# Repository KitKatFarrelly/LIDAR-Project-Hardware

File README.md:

# What is this??
This is the KiCAD files for the PCB and schematic of several iterations of my LIDAR sensor board.
The goal of this board is a wifi-enabled LIDAR sensor that also collects direction and acceleration data via IMU and can act as a flight controller.

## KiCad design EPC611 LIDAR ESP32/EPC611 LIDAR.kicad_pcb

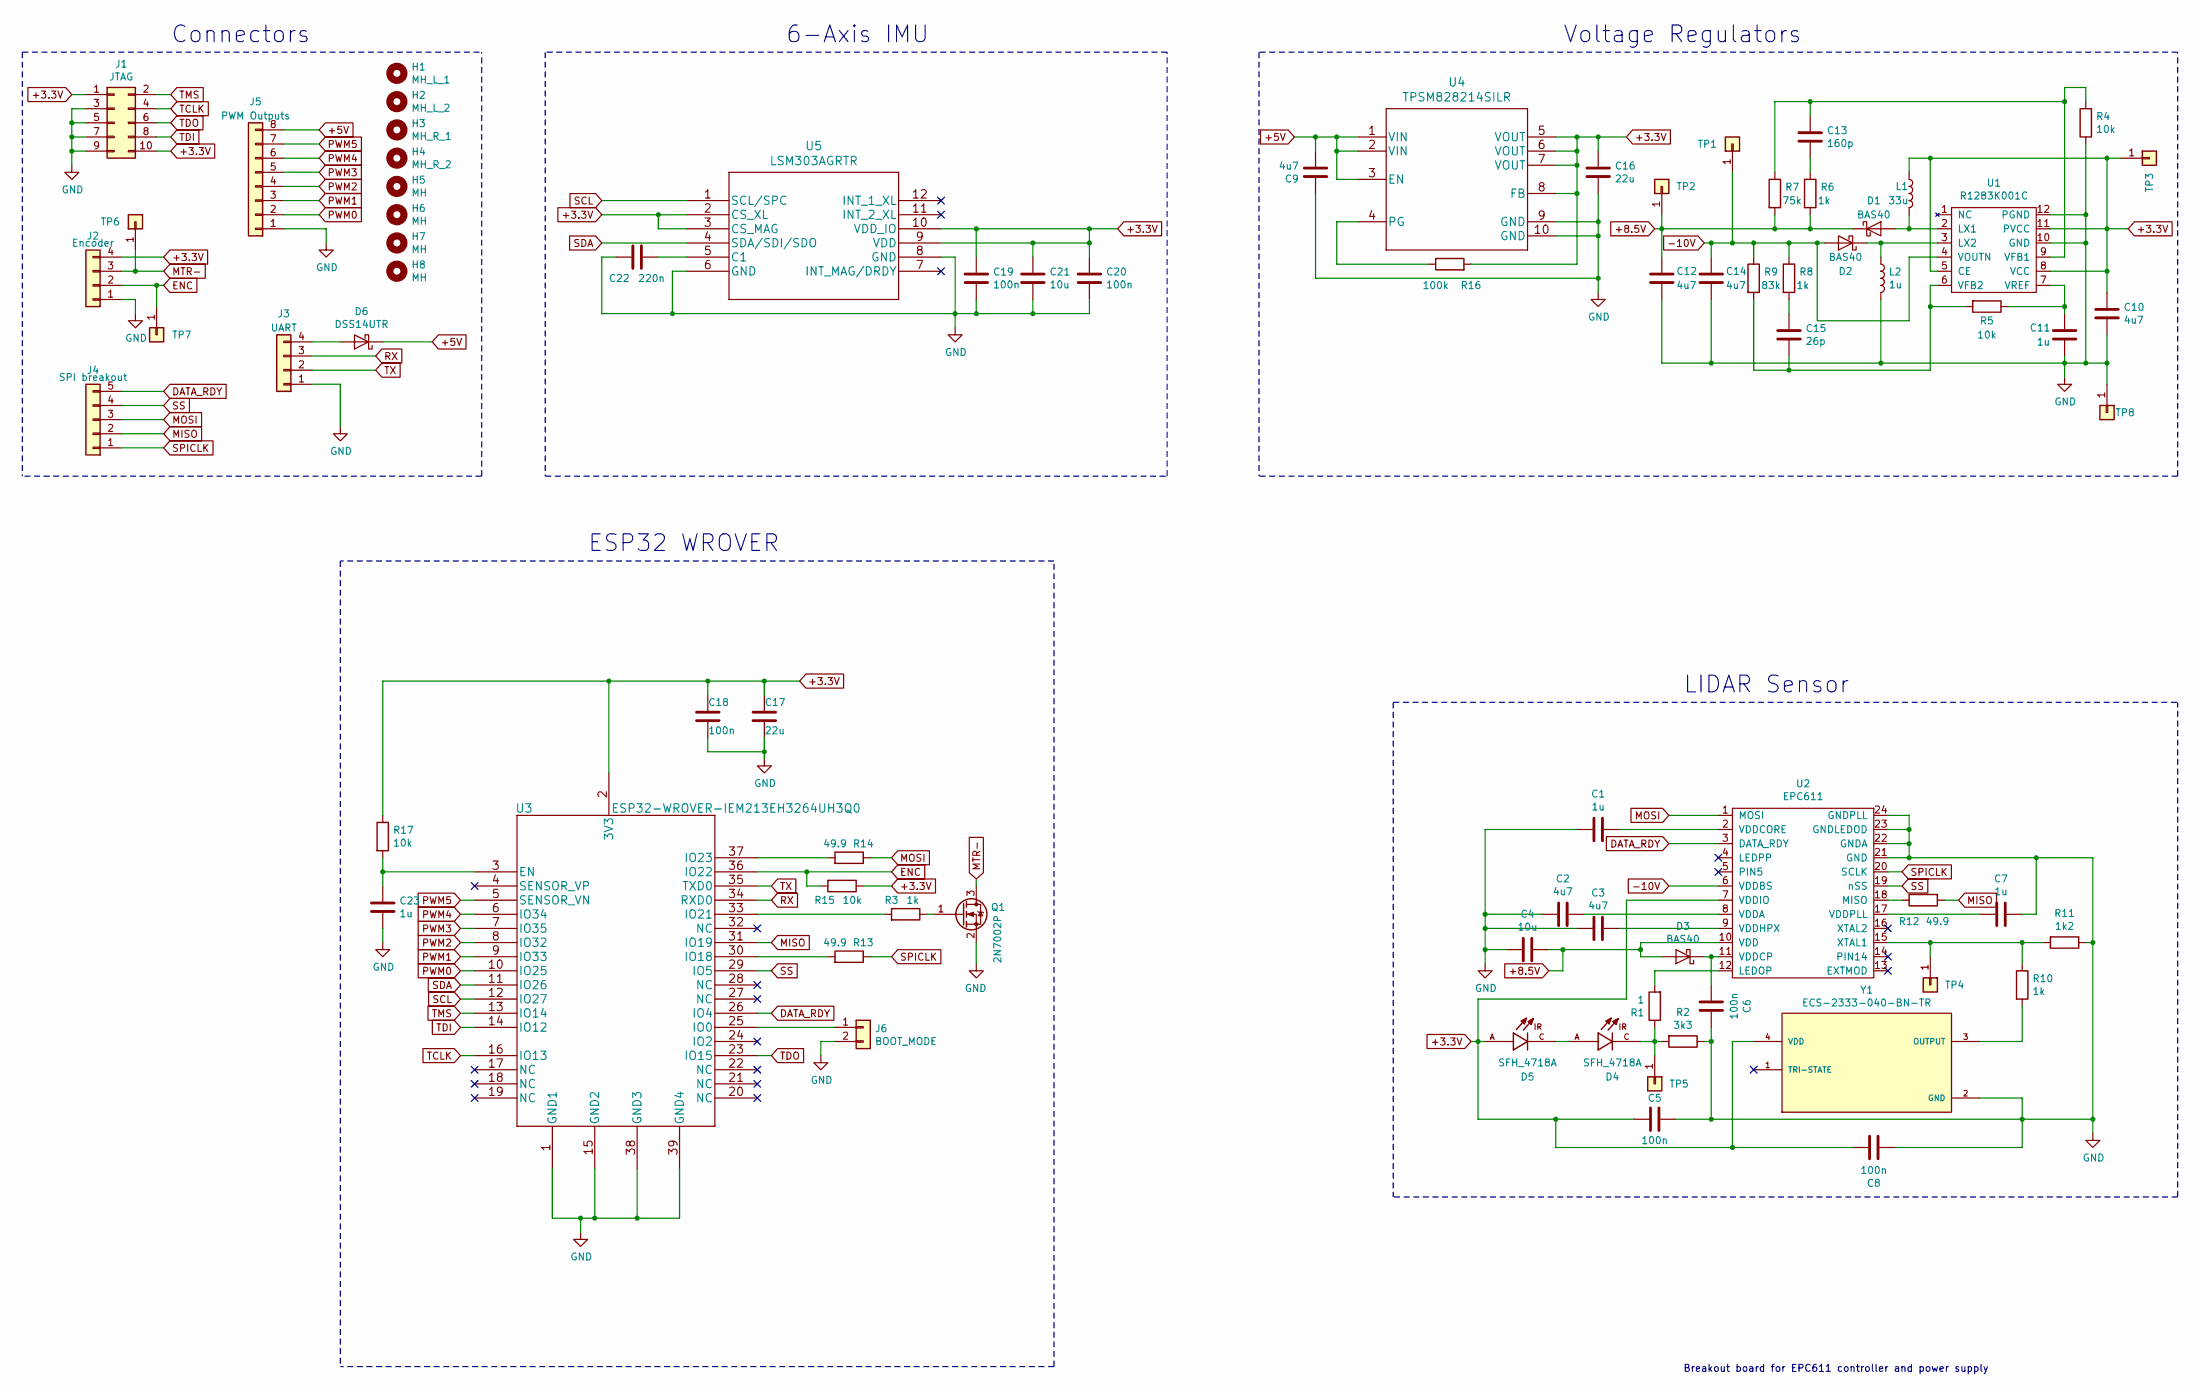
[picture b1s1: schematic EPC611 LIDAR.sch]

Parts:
C1, C7, C11, C23: 1u; C_0603_1608Metric
C2, C3, C9, C10, C12, C14: 4u7; C_0603_1608Metric
C4, C21: 10u; C_0805_2012Metric
C5, C6, C8, C18, C19, C20: 100n; C_0402_1005Metric
C13: 160p; C_0402_1005Metric
C15: 26p; C_0402_1005Metric
C16, C17: 22u; C_0805_2012Metric
C22: 220n; C_0402_1005Metric
D1, D2, D3: BAS40; D_SOT-23_ANK
D4, D5: SFH_4718A; LED_SFH_4718A; PARTREV 1.4
D6: DSS14UTR; D_SOD-123F
H1: MH_L_1; MountingHole_2.2mm_M2
H2: MH_L_2; MountingHole_2.2mm_M2
H3: MH_R_1; MountingHole_2.2mm_M2
H4: MH_R_2; MountingHole_2.2mm_M2
H5, H6, H7, H8: MH; MountingHole_3.2mm_M3
J1: JTAG; PinHeader_2x05_P1.27mm_Vertical_SMD
J2: Encoder; Molex_PicoBlade_53261-0471_1x04-1MP_P1.25mm_Horizontal
J3: UART; Molex_PicoBlade_53261-0471_1x04-1MP_P1.25mm_Horizontal
J4: SPI breakout; spi line debug
J5: PWM Outputs; Molex_PicoBlade_53261-0871_1x08-1MP_P1.25mm_Horizontal
J6: BOOT_MODE; PinHeader_1x02_P1.00mm_Vertical
L1: 33u; L_1008_2520Metric
L2: 1u; L_0603_1608Metric
Q1: 2N7002P; SOT-23
R1: 1; R_0805_2012Metric
R2: 3k3; R_0402_1005Metric
R3, R6, R8, R10: 1k; R_0402_1005Metric
R4, R5, R15, R17: 10k; R_0402_1005Metric
R7: 75k; R_0402_1005Metric
R9: 83k; R_0402_1005Metric
R11: 1k2; R_0402_1005Metric
R12, R13, R14: 49.9; R_0402_1005Metric
R16: 100k; R_0201_0603Metric
TP1, TP2, TP3, TP4, TP5, TP6, TP7, TP8: Conn_01x01; test point
U1: R1283K001C; R1283x
U2: EPC611
U3: ESP32-WROVER-IEM213EH3264UH3Q0
U4: TPSM828214SILR
U5: LSM303AGRTR
Y1: ECS-2333-040-BN-TR; OSC_ECS-2333-040-BN-TR; PARTREV N/A

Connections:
+3.3V: C5.2, C8.1, C10.1, C16.1, C17.1, C18.1, C19.1, C20.1, C21.1, D5.A, J1.1, J1.10, J2.4, L1.1, R15.1, R16.2, R17.1, TP3.1, U1.5 (CE), U1.8 (VCC), U1.11 (PVCC), U2.7 (VDDIO), U3.2 (3V3), U4.5 (VOUT), U4.6 (VOUT), U4.7 (VOUT), U4.8 (FB), U5.2 (CS_XL), U5.3 (CS_MAG), U5.9 (VDD), U5.10 (VDD_IO), Y1.4 (VDD)
+5V: C9.2, D6.1 (K), J5.8, U4.1 (VIN), U4.2 (VIN), U4.3 (EN)
+8.5V: C4.1, C12.1, D1.1 (K), D3.2 (A), R6.2, R7.2, TP2.1, U2.10 (VDD)
-10V: C14.1, D2.2 (A), R8.1, R9.1, TP1.1, U1.4 (VOUTN), U2.6 (VDDBS)
DATA_RDY: J4.5, U2.3 (DATA_RDY), U3.26 (IO4)
ENC: J2.2, R15.2, TP7.1, U3.36 (IO22)
GND: C1.2, C2.2, C3.2, C4.2, C5.1, C6.1, C7.1, C8.2, C9.1, C10.2, C11.2, C12.2, C14.2, C16.2, C17.2, C18.2, C19.2, C20.2, C21.2, C22.1, C23.2, J1.3, J1.5, J1.7, J1.9, J2.1, J3.1, J5.1, J6.2, L2.2, Q1.2 (S), R2.1, R4.1, R11.1, TP8.1, U1.10 (GND), U1.12 (PGND), U2.21 (GND), U2.22 (GNDA), U2.23 (GNDLEDOD), U2.24 (GNDPLL), U3.1 (GND1), U3.15 (GND2), U3.38 (GND3), U3.39 (GND4), U4.9 (GND), U4.10 (GND), U5.6 (GND), U5.8 (GND), Y1.2 (GND)
MISO: J4.2, R12.2, U3.31 (IO19)
MOSI: J4.3, R14.1, U2.1 (MOSI)
MTR-: J2.3, Q1.3 (D), TP6.1
unnamed: C1.1, U2.2 (VDDCORE)
unnamed: C2.1, U2.8 (VDDA)
unnamed: C3.1, U2.9 (VDDHPX)
unnamed: C6.2, D3.1 (K), U2.11 (VDDCP)
unnamed: C7.2, U2.17 (VDDPLL)
unnamed: C11.1, R5.1, U1.7 (VREF)
unnamed: C13.1, R4.2, R7.1, U1.9 (VFB1)
unnamed: C13.2, R6.1
unnamed: C15.1, R8.2
unnamed: C15.2, R5.2, R9.2, U1.6 (VFB2)
unnamed: C22.2, U5.5 (C1)
unnamed: C23.1, R17.2, U3.3 (EN)
unnamed: D1.2 (A), L1.2, U1.2 (LX1)
unnamed: D2.1 (K), L2.1, U1.3 (LX2)
unnamed: D4.A, D5.C
unnamed: D4.C, R1.1, R2.2, TP5.1
unnamed: D6.2 (A), J3.4
unnamed: J6.1, U3.25 (IO0)
unnamed: Q1.1 (G), R3.1
unnamed: R1.2, U2.12 (LEDOP)
unnamed: R3.2, U3.33 (IO21)
unnamed: R10.1, R11.2, TP4.1, U2.15 (XTAL1)
unnamed: R10.2, Y1.3 (OUTPUT)
unnamed: R12.1, U2.18 (MISO)
unnamed: R13.2, U3.30 (IO18)
unnamed: R14.2, U3.37 (IO23)
unnamed: R16.1, U4.4 (PG)
PWM0: J5.2, U3.10 (IO25)
PWM1: J5.3, U3.9 (IO33)
PWM2: J5.4, U3.8 (IO32)
PWM3: J5.5, U3.7 (IO35)
PWM4: J5.6, U3.6 (IO34)
PWM5: J5.7, U3.5 (SENSOR_VN)
RX: J3.3, U3.34 (RXD0)
SCL: U3.12 (IO27), U5.1 (SCL/SPC)
SDA: U3.11 (IO26), U5.4 (SDA/SDI/SDO)
SPICLK: J4.1, R13.1, U2.20 (SCLK)
SS: J4.4, U2.19 (nSS), U3.29 (IO5)
TCLK: J1.4, U3.16 (IO13)
TDI: J1.8, U3.14 (IO12)
TDO: J1.6, U3.23 (IO15)
TMS: J1.2, U3.13 (IO14)
TX: J3.2, U3.35 (TXD0)

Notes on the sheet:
Breakout board for EPC611 controller and power supply
Voltage Regulators
LIDAR Sensor
ESP32 WROVER
Connectors
6-Axis IMU

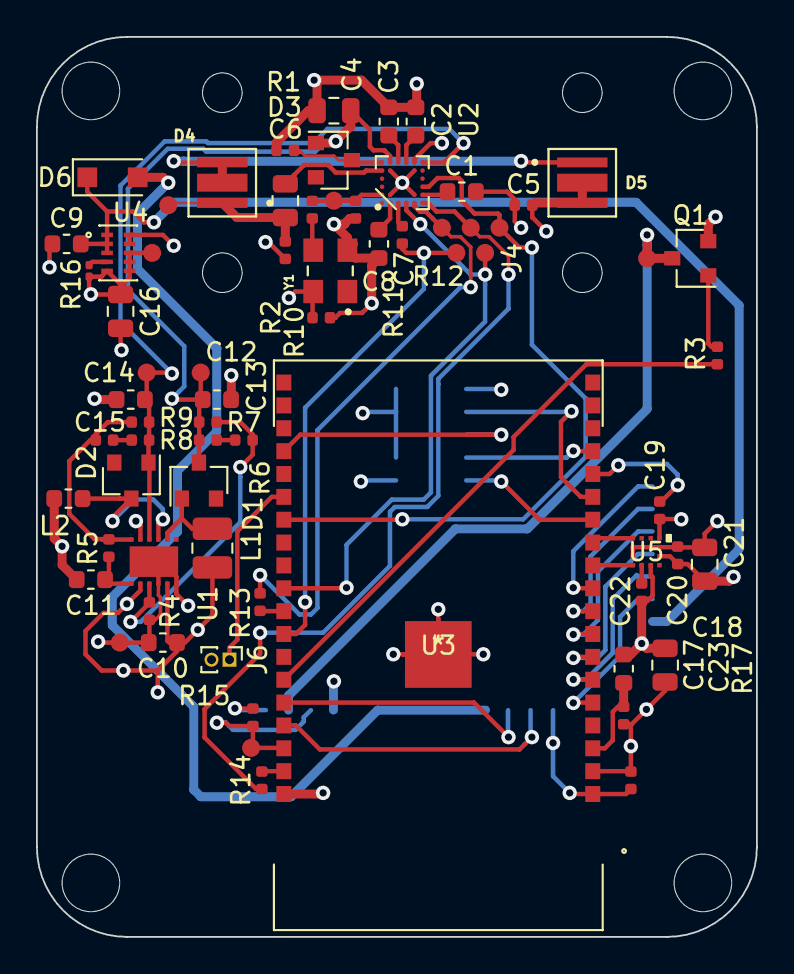
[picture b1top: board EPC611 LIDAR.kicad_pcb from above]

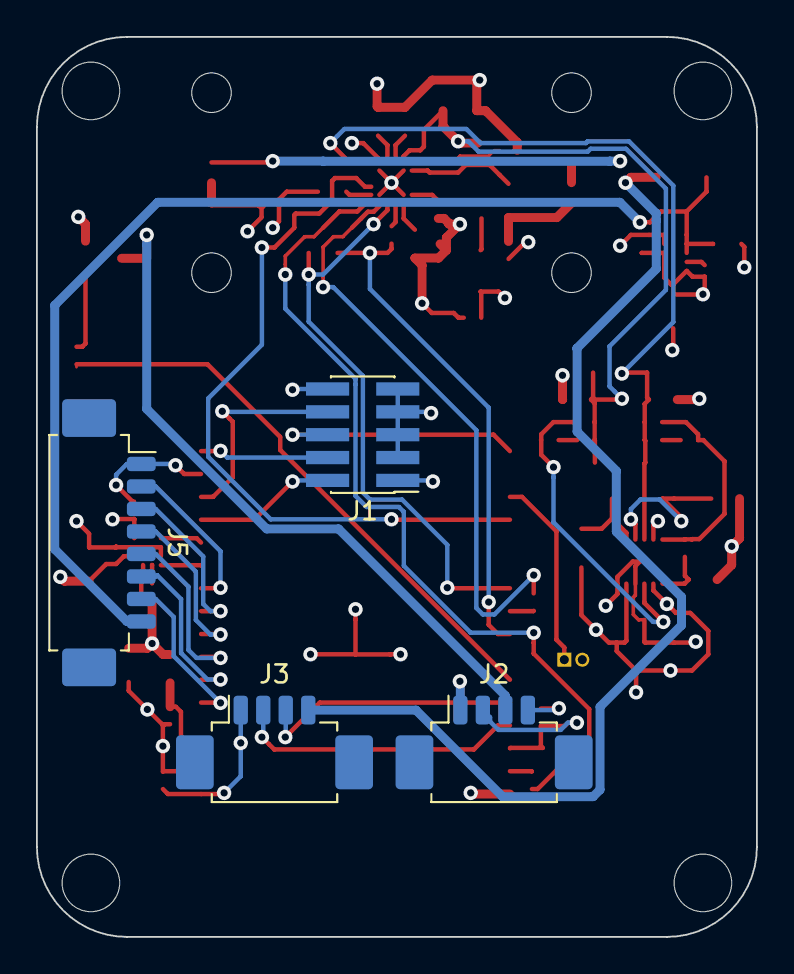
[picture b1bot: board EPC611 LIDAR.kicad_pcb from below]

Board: 4 copper layers, 40.0 x 50.0 mm, 77 parts (4 on the bottom side), 53 nets.

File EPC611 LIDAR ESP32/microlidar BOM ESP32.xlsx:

Line Item | Component Type | Part | Manufacturer | Manufacturer PN | References | Quantity | Footprint | Type | Tolerance | Wattage | Voltage Rating | Generic OK? | Notes
1 | Capacitor | 1u Cap | Samsung | CL10B105KA8NNNC | C1,C7,C11,C23 | 4 | 0603 | SMD |  |  | 25V | Yes
2 | Capacitor | 4.7u Cap | Murata | GRM188R61E475KE11D | C2,C3,C9,C10,C12,C14 | 6 | 0603 | SMD |  |  | 35V | Yes
3 | Capacitor | 10u Cap | Samsung | CL21X106KAYNNNE | C4,C21 | 2 | 0805 | SMD |  |  | 25V | Yes
4 | Capacitor | 100n Cap | Samsung | CL05B104KA5NNNC | C5,C6,C8,C18,C19,C20 | 6 | 0402 | SMD |  |  | 25V | Yes
5 | Capacitor | 166p Cap | Murata | GCM1555C1H161FA16D | C13 | 1 | 0402 | SMD |  |  | 50V | Yes
6 | Capacitor | 26p Cap | AVX Corporation | 04025A270JAT2A | C15 | 1 | 0402 | SMD |  |  | 50V | Yes
7 | Capacitor | 22u Cap | YAGEO | CC0805MKX5R8BB226 | C16,C17 | 2 | 0805 | SMD |  |  | 25V | Yes
8 | Capacitor | 220n Cap | Murata | GRM155C8YA224KE01D | C22 | 1 | 0402 | SMD |  |  | 25V | Yes
9 | Diode | Schottky | Micro Commercial Co | BAS40-TP | D1,D2,D3 | 3 | SOT-23 | SMD
10 | Diode | LED | OSRAM | SFH 4718A | D4,D5 | 2 | 3-SMD | SMD
11 | Diode | Schottky | SMC Diode Solutions | DSS14UTR | D6 | 1 | SOD-123F | SMD
12 | Inductor | 33u Ind | Taiyo Yuden | CB2518T330K | L1 | 1 | 1008 | SMD
13 | Inductor | 1u Ind | TDK Corporation | MLZ1608A1R0WT000 | L2 | 1 | 0603 | SMD
14 | Connector | 10 pin JTAG | CNC Tech | 3220-10-0300-00-TR | J1 | 1 | SMT 10P | SMD |  |  |  |  | DNP
15 | Connector | 4 pin Molex | Molex | 53261-0471 | J2,J3 | 2 | SMT 4P | SMD |  |  |  |  | DNP
16 | Connector | 8 pin Molex | Molex | 53261-0871 | J5 | 1 | SMT 8P | SMD |  |  |  |  | DNP
17 | Connector | 2 pin header | GCT | BC020-02-A-0200-0300-L-G | J6 | 1 | THRU 2P | Through Hole |  |  | 250V
18 | Transistor | NMOSFET | Nexperia USA Inc. | 2N7002P,215 | Q1 | 1 | SOT-23 | SMD
19 | Resistor | 1 Res | Stackpole Electronics | RNCP0805FTD1R00 | R1 | 1 | 0805 | SMD | 1% | 1/4 W |  | Yes
20 | Resistor | 3.3k Res | Panasonic | ERJ-2GEJ332X | R2 | 1 | 0402 | SMD | 1% | 1/10 W |  | Yes
21 | Resistor | 1k Res | YAGEO | RC0402FR-7W1KL | R3,R6,R8,R10 | 4 | 0402 | SMD | 1% | 1/8 W |  | Yes
22 | Resistor | 10k Res | YAGEO | AC0402FR-7W10KL | R4,R5,R15,R17 | 4 | 0402 | SMD | 1% | 1/8 W |  | Yes
23 | Resistor | 75k Res | Stackpole Electronics | RMCF0402FT75K0 | R7 | 1 | 0402 | SMD | 1% | 1/16 W |  | Yes
24 | Resistor | 82.5k Res | Samsung | RC1005F8252CS | R9 | 1 | 0402 | SMD | 1% | 1/16 W |  | Yes
25 | Resistor | 1.2k Res | Panasonic | ERJ-U02F1201X | R11 | 1 | 0402 | SMD | 1% | 1/10 W |  | Yes
26 | Resistor | 49.9 Res | YAGEO | AF0402FR-0749R9L | R12,R13,R14 | 3 | 0402 | SMD | 1% | 1/16 W |  | Yes
27 | Resistor | 100k Res | YAGEO | RC0201JR-07100KL | R16 | 1 | 0201 | SMD | 1% | 1/20 W |  | Yes
28 | Integrated Circuit | Regulator | RICOH | R1283K001C-TR | U1 | 1 | 12-UFDFN | SMD
29 | Integrated Circuit | LIDAR | ESPROS | EPC611-CSP24-001 | U2 | 1 | 24-CSP | SMD
30 | Integrated Circuit | ESP32-WROVER | Expressif Systems | ESP32-WROVER-IE (4MB) | U3 | 1 | 56-VFQFN | SMD |  |  |  |  | ESP32-WROVER(M203QL3264PH3Q0) is an acceptable substitute
31 | Integrated Circuit | Regulator | Texas Instruments | TPSM828214SILR | U4 | 1 | 10-uSIP | SMD
32 | Integrated Circuit | IMU | STMicroelectronics | LSM303AGRTR | U5 | 1 | 12-VFLGA | SMD |  |  |  |  | DNP
33 | Oscillator | 4MHz | ECS Inc. | ECS-2333-040-BN-TR | Y1 | 1 | 4-SMD | SMD
Generic OK: For Generic Components, the Footprint and Value must match. The Wat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

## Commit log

2022-03-21 Initial Commit
    adding all the hardware files
2022-10-16 added some 3D models

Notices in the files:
parts and their libraries:
Copyright 2021 Accelerated Designs. All rights reserved.
